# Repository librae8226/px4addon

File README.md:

px4addon
========

Power distribution board with further/misc objectives.
Mainly used for stack assembling with px4fmu + px4io.

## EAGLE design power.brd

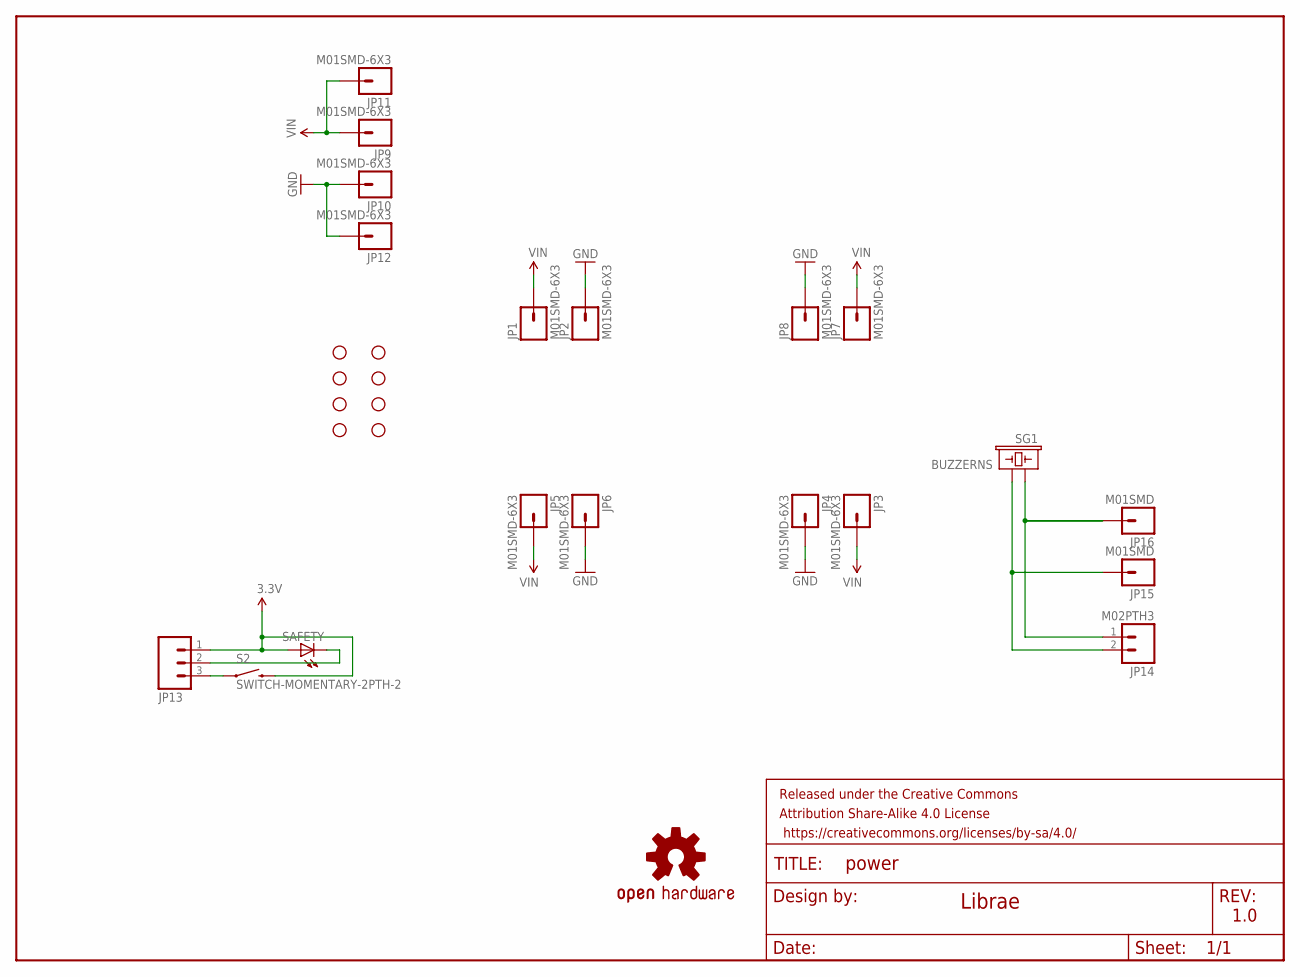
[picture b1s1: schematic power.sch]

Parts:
FRAME1: FRAME-LETTER; CREATIVE_COMMONS
JP1, JP2, JP3, JP4, JP5, JP6, JP7, JP8, JP9, JP10, JP11, JP12: M01SMD-6X3; PAD-BULLET
JP13: M03LONGPADS; 1X03_LONGPADS
JP14: M02PTH3; 1X02_LONGPADS
JP15, JP16: M01SMD; LUXEON-PAD
LOGO1: OSHW-LOGOL; OSHW-LOGO-L
S2: SWITCH-MOMENTARY-2PTH-2; TACTILE-PTH-2
SAFETY: LED5MM
SG1: BUZZERNS; BUZZER-12MM-NS
STANDOFF1, STANDOFF2, STANDOFF3, STANDOFF4, STANDOFF5, STANDOFF6, STANDOFF7, STANDOFF8: STAND-OFF

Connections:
3.3V: JP13.1, S2.4 (2), SAFETY.A
GND: JP2.P$1, JP4.P$1, JP6.P$1, JP8.P$1, JP10.P$1, JP12.P$1
unnamed: JP14.1, JP16.P$1, SG1.+ (1)
unnamed: JP13.3, S2.1
unnamed: JP13.2, SAFETY.K (C)
unnamed: JP14.2, JP15.P$1, SG1.- (2)
VIN: JP1.P$1, JP3.P$1, JP5.P$1, JP7.P$1, JP9.P$1, JP11.P$1

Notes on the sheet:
Librae
1.0

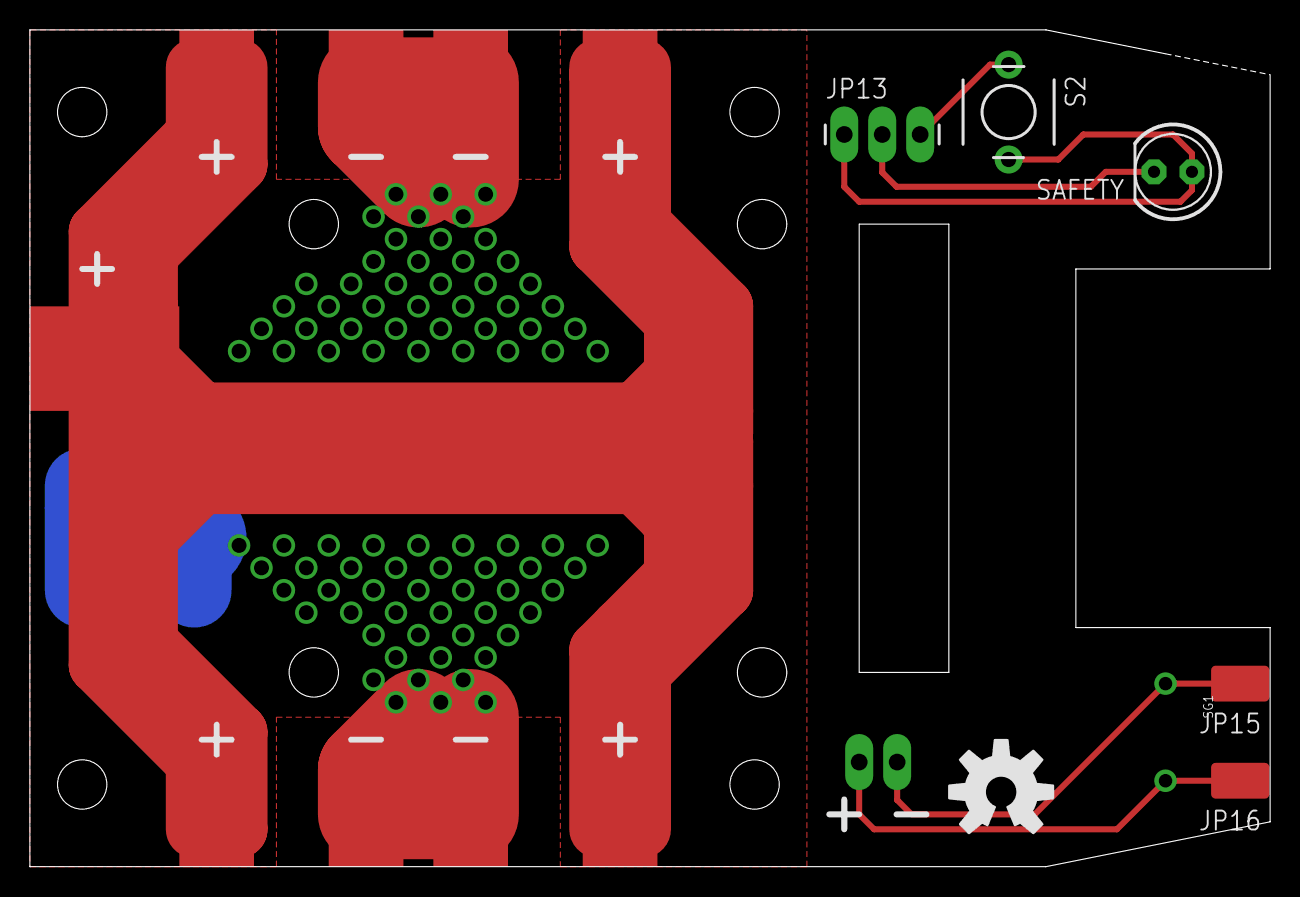
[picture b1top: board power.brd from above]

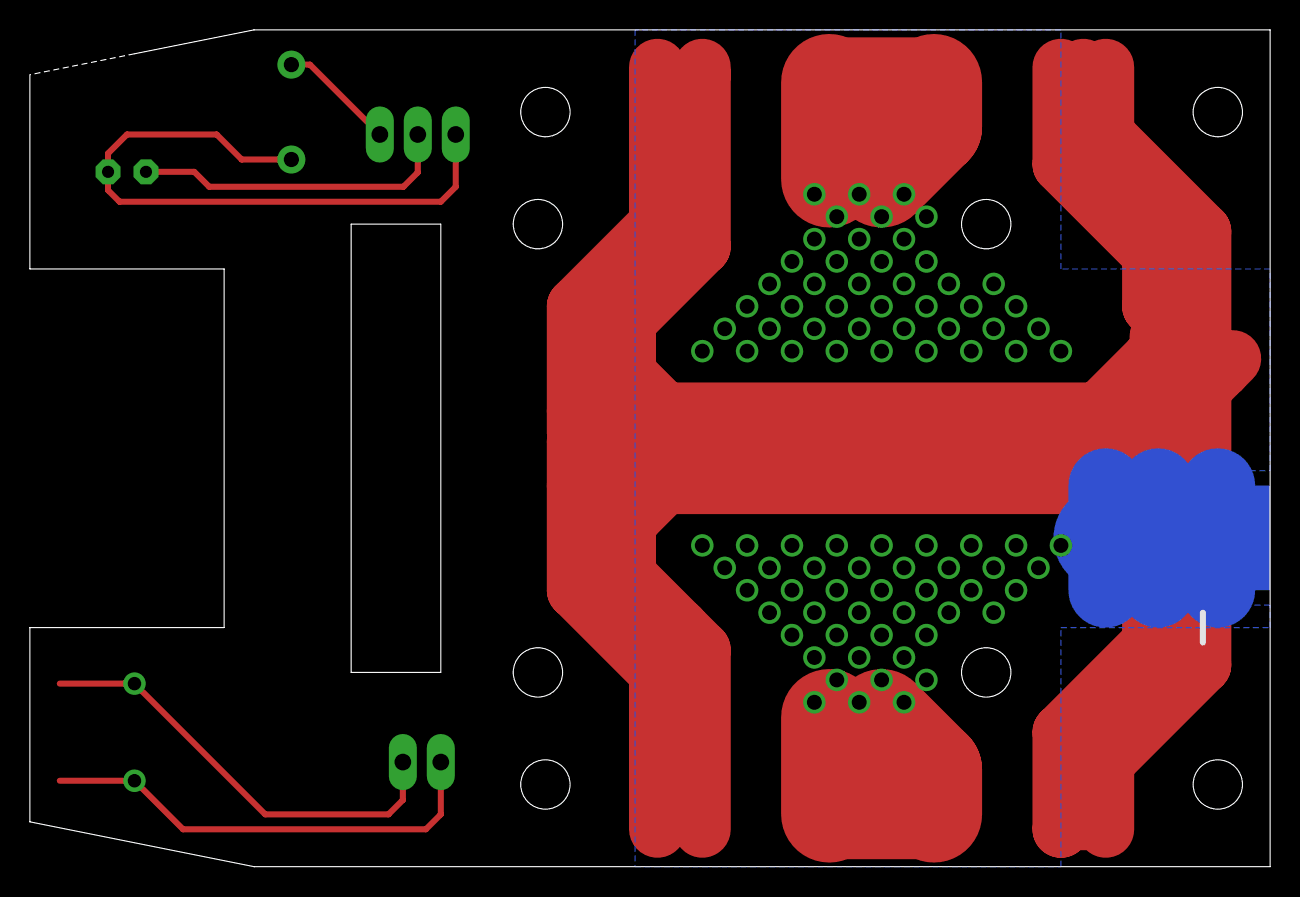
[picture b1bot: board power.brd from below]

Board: 2 copper layers, 83.0 x 56.0 mm, 29 parts (2 on the bottom side), 7 nets.

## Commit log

2014-07-22 init
2014-07-23 slightly modified logo position
2014-07-23 build up the frame work
2014-07-23 update layout
2014-07-23 some minor update
2014-07-23 slightly refine power track
2014-07-25 change drills
2014-07-25 fix some positions
2014-07-25 more fixes
2014-07-25 almost done
2014-07-27 basically done
2014-07-27 minor update

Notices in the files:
parts and their libraries:
SparkFun-Aesthetics: Licensing: Creative Commons ShareAlike 4.0 International - https://creativecommons.org/licenses/by-sa/4.0
SparkFun-Aesthetics: Released under the Creative Commons Attribution Share-Alike 4.0 License
SparkFun-Aesthetics: https://creativecommons.org/licenses/by-sa/4.0
